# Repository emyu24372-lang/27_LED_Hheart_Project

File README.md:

This project consists of 27 LEDs controlled by an ESP32 Mini. It has three modes that can be switched between by pressing a button.
The first mode turns all the LEDs on. In the second mode
each LED turns on and off one by one. In the final mode
all the LEDs pulse together like a beating heart.

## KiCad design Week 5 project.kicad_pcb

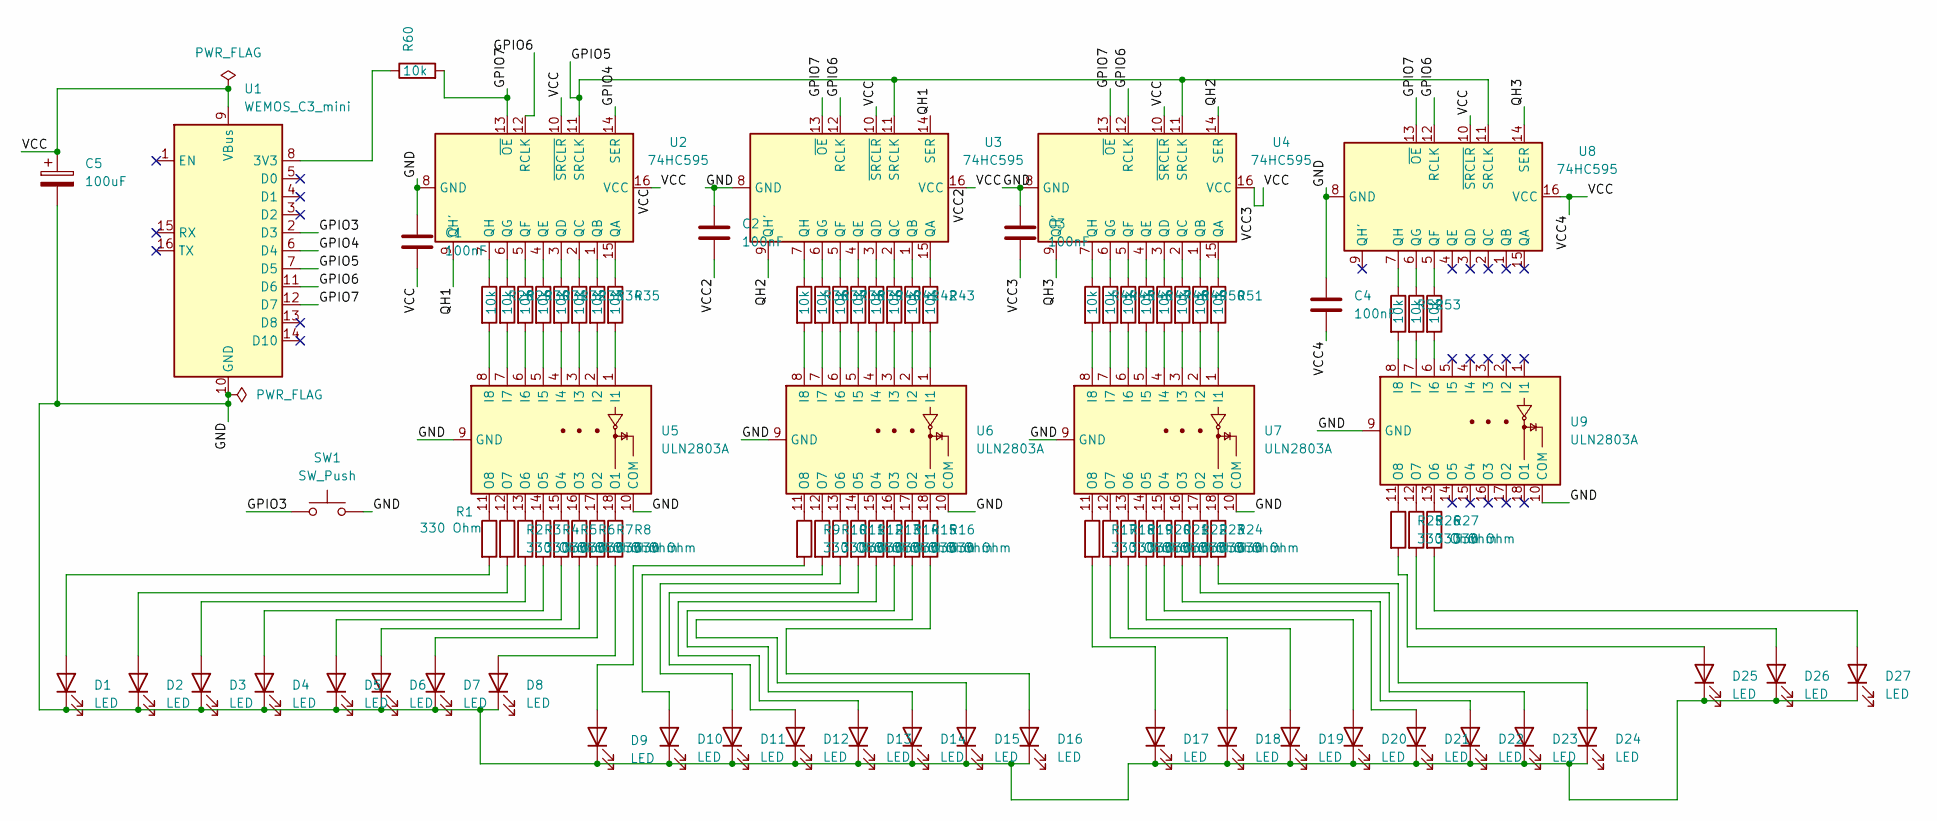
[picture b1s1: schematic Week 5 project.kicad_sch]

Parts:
C1, C2, C3, C4: 100nF; C_0805_2012Metric
C5: 100uF; CP_Elec_6.3x5.4
D1, D2, D3, D4, D5, D6, D7, D8, D9, D10, D11, D12, D13, D14, D15, D16, D17, D18, D19, D20, D21, D22, D23, D24, D25, D26, D27: LED; LED_D5.0mm
R1, R2, R3, R4, R5, R6, R7, R8, R9, R10, R11, R12, R13, R14, R15, R16, R17, R18, R19, R20, R21, R22, R23, R24, R25, R26, R27: 330 Ohm; R_0805_2012Metric
R28, R29, R30, R31, R32, R33, R34, R35, R36, R37, R38, R39, R40, R41, R42, R43, R44, R45, R46, R47, R48, R49, R50, R51, R52, R53, R54, R60: 10k; R_0805_2012Metric
SW1: SW_Push; SW_PUSH_6mm
U1: WEMOS_C3_mini
U2, U3, U4, U8: 74HC595; SOIC-16_3.9x9.9mm_P1.27mm
U5, U6, U7, U9: ULN2803A; SOIC-18W_7.5x11.6mm_P1.27mm

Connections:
/GND: C1.1, C2.1, C3.1, C4.1, C5.2, D1.1 (K), D2.1 (K), D3.1 (K), D4.1 (K), D5.1 (K), D6.1 (K), D7.1 (K), D8.1 (K), D9.1 (K), D10.1 (K), D11.1 (K), D12.1 (K), D13.1 (K), D14.1 (K), D15.1 (K), D16.1 (K), D17.1 (K), D18.1 (K), D19.1 (K), D20.1 (K), D21.1 (K), D22.1 (K), D23.1 (K), D24.1 (K), D25.1 (K), D26.1 (K), D27.1 (K), SW1.2, U1.10 (GND), U2.8 (GND), U3.8 (GND), U4.8 (GND), U5.9 (GND), U5.10 (COM), U6.9 (GND), U6.10 (COM), U7.9 (GND), U7.10 (COM), U8.8 (GND), U9.9 (GND), U9.10 (COM)
/GPIO3: SW1.1, U1.2 (D3)
/GPIO4: U1.6 (D4), U2.14 (SER)
/GPIO5: U1.7 (D5), U2.11 (SRCLK), U3.11 (SRCLK), U4.11 (SRCLK), U8.11 (SRCLK)
/GPIO6: U1.11 (D6), U2.12 (RCLK), U3.12 (RCLK), U4.12 (RCLK), U8.12 (RCLK)
/GPIO7: R60.2, U1.12 (D7), U2.13 (~OE), U3.13 (~OE), U4.13 (~OE), U8.13 (~OE)
/QH1: U2.9 (QH'), U3.14 (SER)
/QH2: U3.9 (QH'), U4.14 (SER)
/QH3: U4.9 (QH'), U8.14 (SER)
/VCC: C1.2, C2.2, C3.2, C4.2, C5.1, U1.9 (VBus), U2.10 (~SRCLR), U2.16 (VCC), U3.10 (~SRCLR), U3.16 (VCC), U4.10 (~SRCLR), U4.16 (VCC), U8.10 (~SRCLR), U8.16 (VCC)
unnamed: D1.2 (A), R1.2
unnamed: D2.2 (A), R2.2
unnamed: D3.2 (A), R3.2
unnamed: D4.2 (A), R4.2
unnamed: D5.2 (A), R5.2
unnamed: D6.2 (A), R6.2
unnamed: D7.2 (A), R7.2
unnamed: D8.2 (A), R8.2
unnamed: D9.2 (A), R9.2
unnamed: D10.2 (A), R10.2
unnamed: D11.2 (A), R11.2
unnamed: D12.2 (A), R12.2
unnamed: D13.2 (A), R13.2
unnamed: D14.2 (A), R14.2
unnamed: D15.2 (A), R15.2
unnamed: D16.2 (A), R16.2
unnamed: D17.2 (A), R17.2
unnamed: D18.2 (A), R18.2
unnamed: D19.2 (A), R19.2
unnamed: D20.2 (A), R20.2
unnamed: D21.2 (A), R21.2
unnamed: D22.2 (A), R22.2
unnamed: D23.2 (A), R23.2
unnamed: D24.2 (A), R24.2
unnamed: D25.2 (A), R25.2
unnamed: D26.2 (A), R26.2
unnamed: D27.2 (A), R27.2
unnamed: R60.1, U1.8 (3V3)
unnamed: R35.1, U2.15 (QA)
unnamed: R34.1, U2.1 (QB)
unnamed: R33.1, U2.2 (QC)
unnamed: R32.1, U2.3 (QD)
unnamed: R31.1, U2.4 (QE)
unnamed: R30.1, U2.5 (QF)
unnamed: R29.1, U2.6 (QG)
unnamed: R28.1, U2.7 (QH)
unnamed: R43.1, U3.15 (QA)
unnamed: R42.1, U3.1 (QB)
unnamed: R41.1, U3.2 (QC)
unnamed: R40.1, U3.3 (QD)
unnamed: R39.1, U3.4 (QE)
unnamed: R38.1, U3.5 (QF)
unnamed: R37.1, U3.6 (QG)
unnamed: R36.1, U3.7 (QH)
unnamed: R51.1, U4.15 (QA)
unnamed: R50.1, U4.1 (QB)
unnamed: R49.1, U4.2 (QC)
unnamed: R48.1, U4.3 (QD)
unnamed: R47.1, U4.4 (QE)
unnamed: R46.1, U4.5 (QF)
unnamed: R45.1, U4.6 (QG)
unnamed: R44.1, U4.7 (QH)
unnamed: R35.2, U5.1 (I1)
unnamed: R34.2, U5.2 (I2)
unnamed: R33.2, U5.3 (I3)
unnamed: R32.2, U5.4 (I4)
unnamed: R31.2, U5.5 (I5)
unnamed: R30.2, U5.6 (I6)
unnamed: R29.2, U5.7 (I7)
unnamed: R28.2, U5.8 (I8)
unnamed: R8.1, U5.18 (O1)
unnamed: R7.1, U5.17 (O2)
unnamed: R6.1, U5.16 (O3)
unnamed: R5.1, U5.15 (O4)
unnamed: R4.1, U5.14 (O5)
unnamed: R3.1, U5.13 (O6)
unnamed: R2.1, U5.12 (O7)
unnamed: R1.1, U5.11 (O8)
unnamed: R43.2, U6.1 (I1)
unnamed: R42.2, U6.2 (I2)
unnamed: R41.2, U6.3 (I3)
unnamed: R40.2, U6.4 (I4)
unnamed: R39.2, U6.5 (I5)
unnamed: R38.2, U6.6 (I6)
unnamed: R37.2, U6.7 (I7)
unnamed: R36.2, U6.8 (I8)
unnamed: R16.1, U6.18 (O1)
unnamed: R15.1, U6.17 (O2)
unnamed: R14.1, U6.16 (O3)
unnamed: R13.1, U6.15 (O4)
unnamed: R12.1, U6.14 (O5)
unnamed: R11.1, U6.13 (O6)
unnamed: R10.1, U6.12 (O7)
unnamed: R9.1, U6.11 (O8)
unnamed: R51.2, U7.1 (I1)
unnamed: R50.2, U7.2 (I2)
unnamed: R49.2, U7.3 (I3)
unnamed: R48.2, U7.4 (I4)
unnamed: R47.2, U7.5 (I5)
unnamed: R46.2, U7.6 (I6)
unnamed: R45.2, U7.7 (I7)
unnamed: R44.2, U7.8 (I8)
unnamed: R24.1, U7.18 (O1)
unnamed: R23.1, U7.17 (O2)
unnamed: R22.1, U7.16 (O3)
unnamed: R21.1, U7.15 (O4)
unnamed: R20.1, U7.14 (O5)
unnamed: R19.1, U7.13 (O6)
unnamed: R18.1, U7.12 (O7)
unnamed: R17.1, U7.11 (O8)
unnamed: R54.1, U8.5 (QF)
unnamed: R53.1, U8.6 (QG)
unnamed: R52.1, U8.7 (QH)
unnamed: R54.2, U9.6 (I6)
unnamed: R53.2, U9.7 (I7)
unnamed: R52.2, U9.8 (I8)
unnamed: R27.1, U9.13 (O6)
unnamed: R26.1, U9.12 (O7)
unnamed: R25.1, U9.11 (O8)

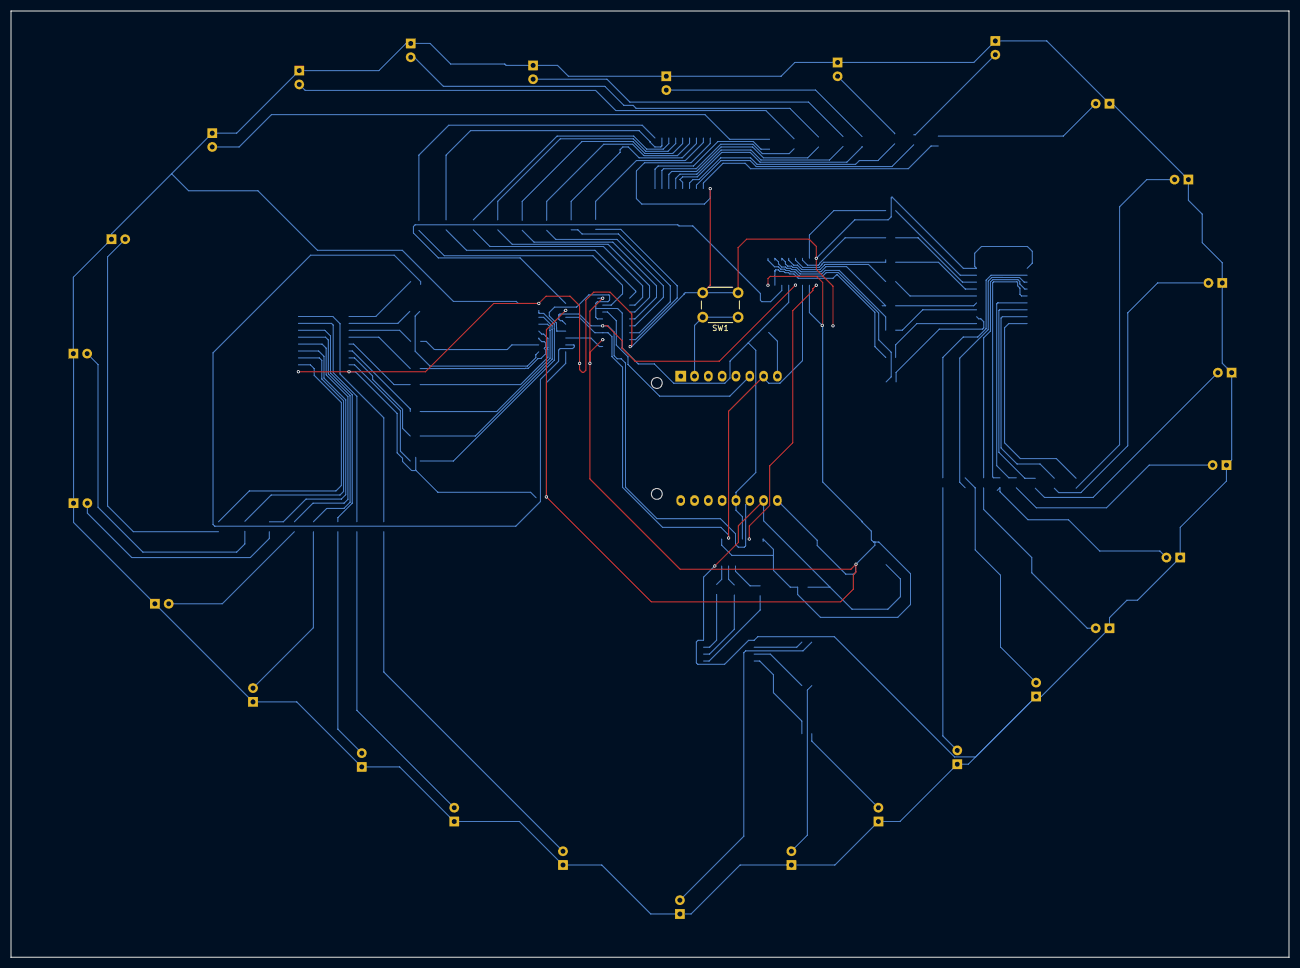
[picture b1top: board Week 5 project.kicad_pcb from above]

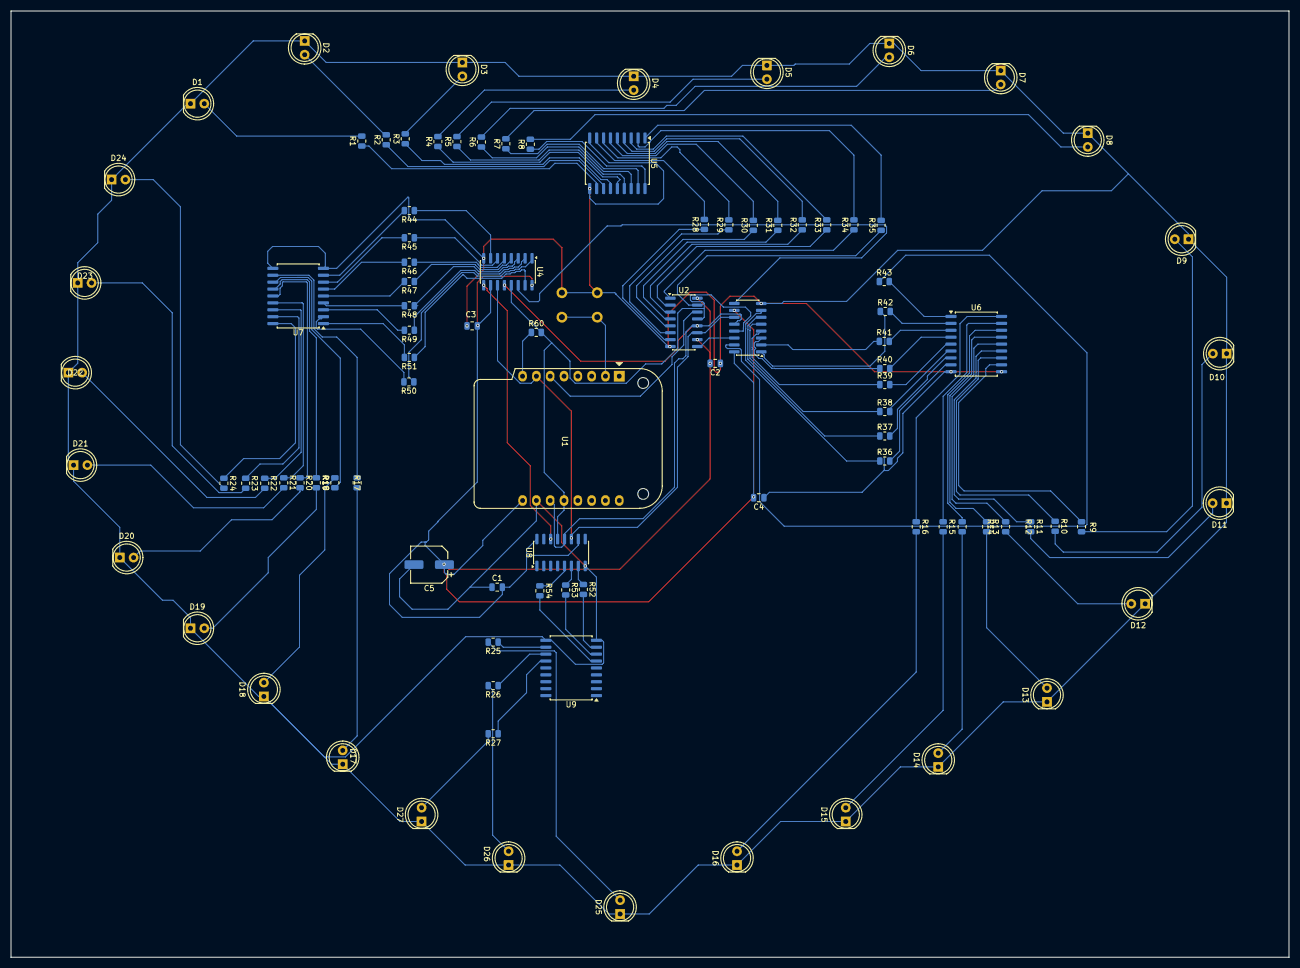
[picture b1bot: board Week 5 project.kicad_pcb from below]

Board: 2 copper layers, 235.0 x 174.0 mm, 97 parts (96 on the bottom side), 119 nets.
